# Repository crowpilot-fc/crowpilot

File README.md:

<!-- SPDX-License-Identifier: CC-BY-SA-4.0 -->
<!-- Copyright (C) 2026 Nitin Kumar -->

# CrowPilot

CrowPilot is an experimental fixed-wing flight controller for the RP2350A.
The rebuild is intentionally limited to one receiver protocol and one safe
bring-up path:

- WeAct RP2350A V10 controller module
- SBUS receiver input
- Eight standard PWM outputs
- MPU6500 over SPI
- BMP388 over I2C
- MicroSD blackbox logging
- Optional ESP32 field companion, electrically disabled while armed

The flight firmware is being rebuilt on the Raspberry Pi Pico SDK. It has not
been flight-tested. Do not install a propeller or connect a motor capable of
producing thrust during development or initial bench testing.

The current architecture and implementation plan are maintained in
[Notion](https://app.notion.com/p/3d0f4e695ae381d5b3c9dfaea4ba3e7e).
The authoritative physical BOM, wiring schedule, and staged assembly checks are
in the [Rebuild V1 bench carrier build pack](https://app.notion.com/p/3d0f4e695ae3812eb996db04cc5e7621).

## Host tests

```sh
cmake -S . -B build/host -G Ninja
cmake --build build/host
ctest --test-dir build/host --output-on-failure
```

## RP2350 firmware

Install the Raspberry Pi Pico SDK and Arm embedded toolchain, then run:

```sh
PICO_SDK_PATH=/path/to/pico-sdk cmake -S firmware -B build/firmware -G Ninja
cmake --build build/firmware
```

The first firmware milestone only implements safe PWM initialization, SBUS
manual passthrough, arming, receiver-loss failsafe, and a watchdog. Sensors,
logging, the companion, and stabilization are tracked as later milestones.

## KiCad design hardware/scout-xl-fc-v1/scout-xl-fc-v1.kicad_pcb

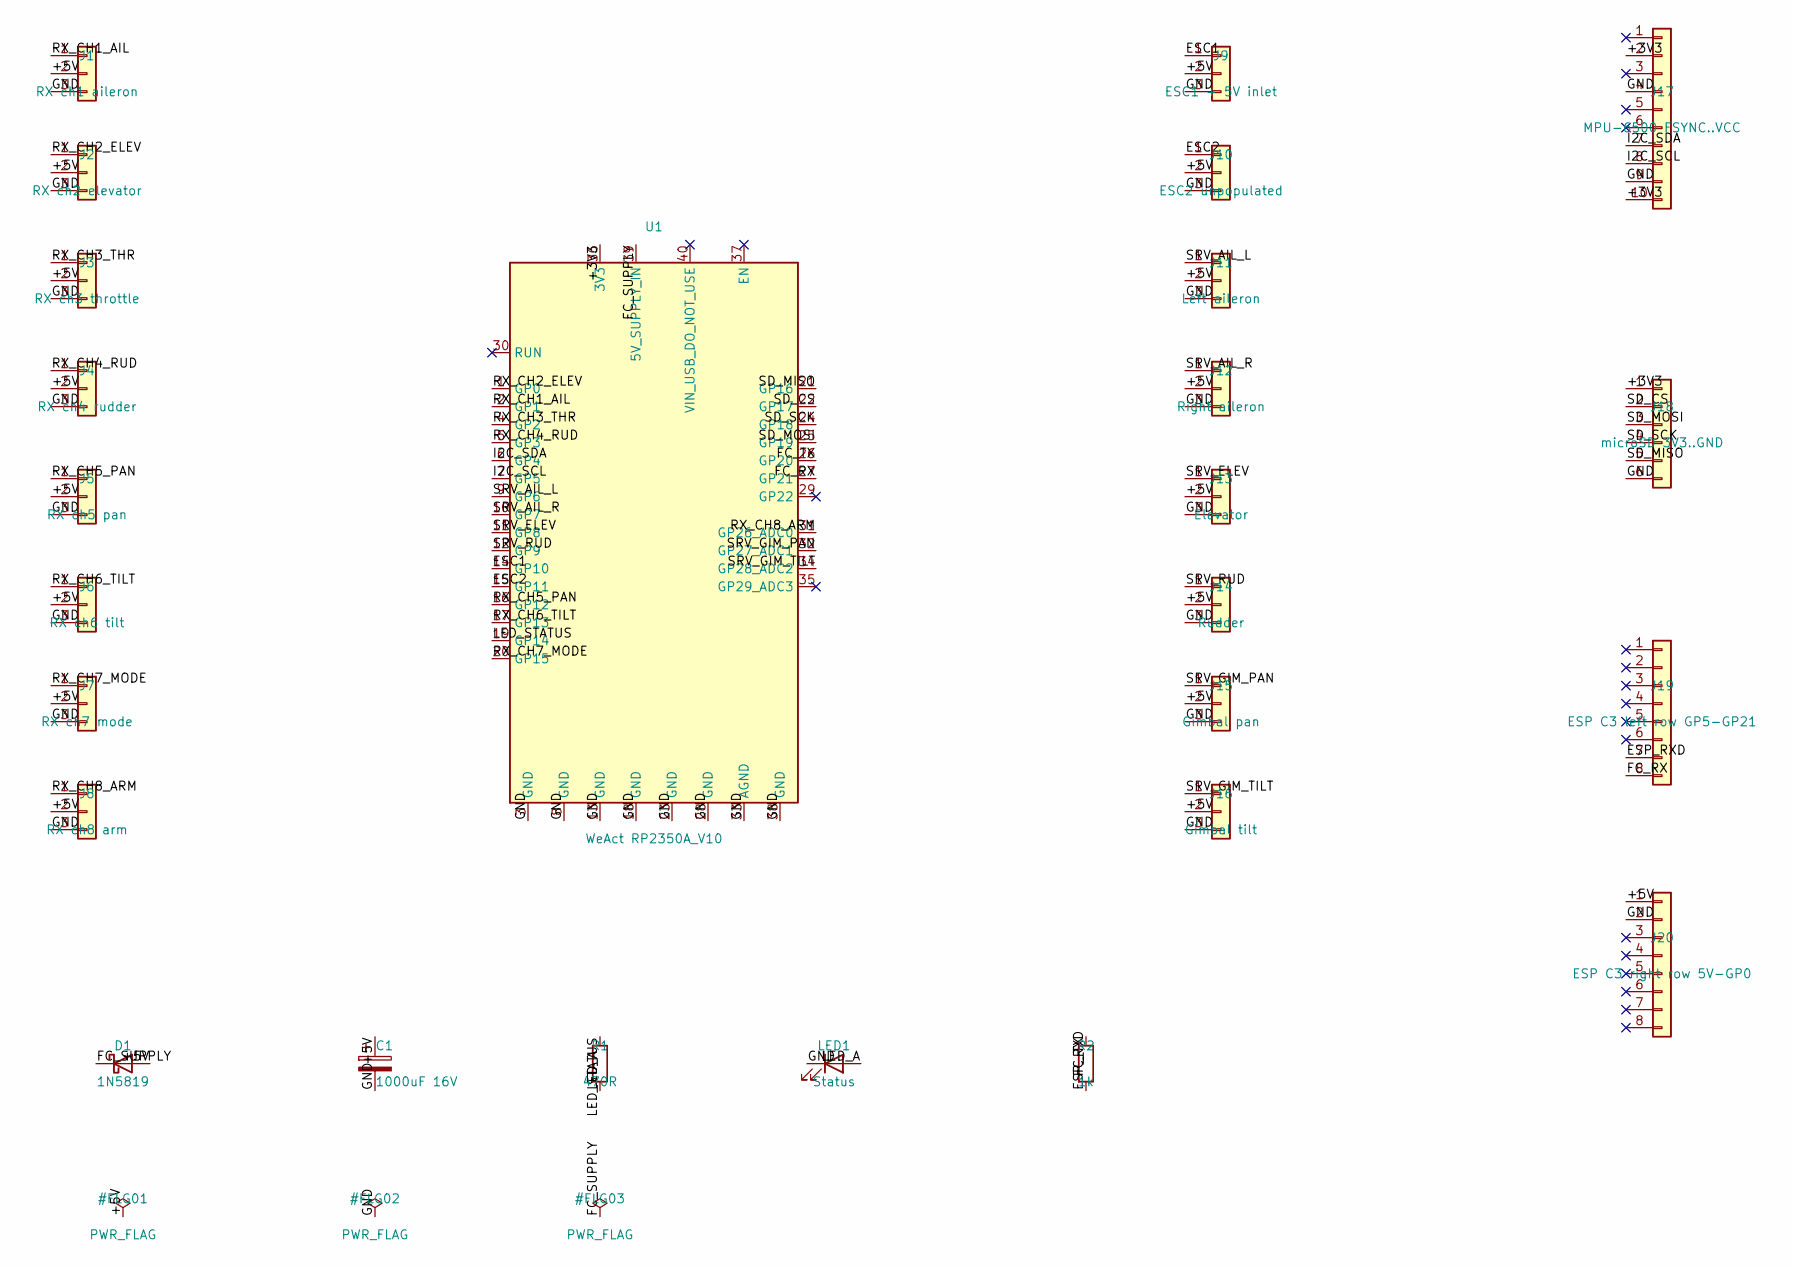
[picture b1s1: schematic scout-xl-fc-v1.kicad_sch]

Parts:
C1: 1000uF 16V; CP_Radial_D10.0mm_P5.00mm
D1: 1N5819; D_DO-41_SOD81_P10.16mm_Horizontal
J1: RX ch1 aileron; PinHeader_1x03_P2.54mm_Butt
J2: RX ch2 elevator; PinHeader_1x03_P2.54mm_Butt
J3: RX ch3 throttle; PinHeader_1x03_P2.54mm_Butt
J4: RX ch4 rudder; PinHeader_1x03_P2.54mm_Butt
J5: RX ch5 pan; PinHeader_1x03_P2.54mm_Butt
J6: RX ch6 tilt; PinHeader_1x03_P2.54mm_Butt
J7: RX ch7 mode; PinHeader_1x03_P2.54mm_Butt
J8: RX ch8 arm; PinHeader_1x03_P2.54mm_Butt
J9: ESC1 + 5V inlet; PinHeader_1x03_P2.54mm_Butt
J10: ESC2 unpopulated; PinHeader_1x03_P2.54mm_Butt
J11: Left aileron; PinHeader_1x03_P2.54mm_Butt
J12: Right aileron; PinHeader_1x03_P2.54mm_Butt
J13: Elevator; PinHeader_1x03_P2.54mm_Butt
J14: Rudder; PinHeader_1x03_P2.54mm_Butt
J15: Gimbal pan; PinHeader_1x03_P2.54mm_Butt
J16: Gimbal tilt; PinHeader_1x03_P2.54mm_Butt
J17: MPU-6500 FSYNC..VCC; PinHeader_1x10_P2.54mm_Vertical
J18: microSD 3V3..GND; PinHeader_1x06_P2.54mm_Vertical
J19: ESP C3 left row GP5-GP21; PinHeader_1x08_P2.54mm_Vertical
J20: ESP C3 right row 5V-GP0; PinHeader_1x08_P2.54mm_Vertical
LED1: Status; LED_D3.0mm_Clear
R1: 470R; R_Axial_DIN0207_L6.3mm_D2.5mm_P7.62mm_Horizontal
R2: 1k; R_Axial_DIN0207_L6.3mm_D2.5mm_P7.62mm_Horizontal
U1: WeAct RP2350A_V10; RaspberryPi_Pico_Common_THT

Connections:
+3V3: J17.2, J17.10, J18.1, U1.36 (3V3)
+5V: C1.1, D1.2 (A), J1.2, J2.2, J3.2, J4.2, J5.2, J6.2, J7.2, J8.2, J9.2, J10.2, J11.2, J12.2, J13.2, J14.2, J15.2, J16.2, J20.1
ESC1: J9.1, U1.14 (GP10)
ESC2: J10.1, U1.15 (GP11)
ESP_RXD: J19.7, R2.2
FC_RX: J19.8, U1.27 (GP21)
FC_SUPPLY: D1.1 (K), U1.39 (5V_SUPPLY_IN)
FC_TX: R2.1, U1.26 (GP20)
GND: C1.2, J1.3, J2.3, J3.3, J4.3, J5.3, J6.3, J7.3, J8.3, J9.3, J10.3, J11.3, J12.3, J13.3, J14.3, J15.3, J16.3, J17.4, J17.9, J18.6, J20.2, LED1.1 (K), U1.3 (GND), U1.8 (GND), U1.13 (GND), U1.18 (GND), U1.23 (GND), U1.28 (GND), U1.33 (AGND), U1.38 (GND)
I2C_SCL: J17.8, U1.7 (GP5)
I2C_SDA: J17.7, U1.6 (GP4)
LED_A: LED1.2 (A), R1.2
LED_STATUS: R1.1, U1.19 (GP14)
RX_CH1_AIL: J1.1, U1.2 (GP1)
RX_CH2_ELEV: J2.1, U1.1 (GP0)
RX_CH3_THR: J3.1, U1.4 (GP2)
RX_CH4_RUD: J4.1, U1.5 (GP3)
RX_CH5_PAN: J5.1, U1.16 (GP12)
RX_CH6_TILT: J6.1, U1.17 (GP13)
RX_CH7_MODE: J7.1, U1.20 (GP15)
RX_CH8_ARM: J8.1, U1.31 (GP26_ADC0)
SD_CS: J18.2, U1.22 (GP17)
SD_MISO: J18.5, U1.21 (GP16)
SD_MOSI: J18.3, U1.25 (GP19)
SD_SCK: J18.4, U1.24 (GP18)
SRV_AIL_L: J11.1, U1.9 (GP6)
SRV_AIL_R: J12.1, U1.10 (GP7)
SRV_ELEV: J13.1, U1.11 (GP8)
SRV_GIM_PAN: J15.1, U1.32 (GP27_ADC1)
SRV_GIM_TILT: J16.1, U1.34 (GP28_ADC2)
SRV_RUD: J14.1, U1.12 (GP9)

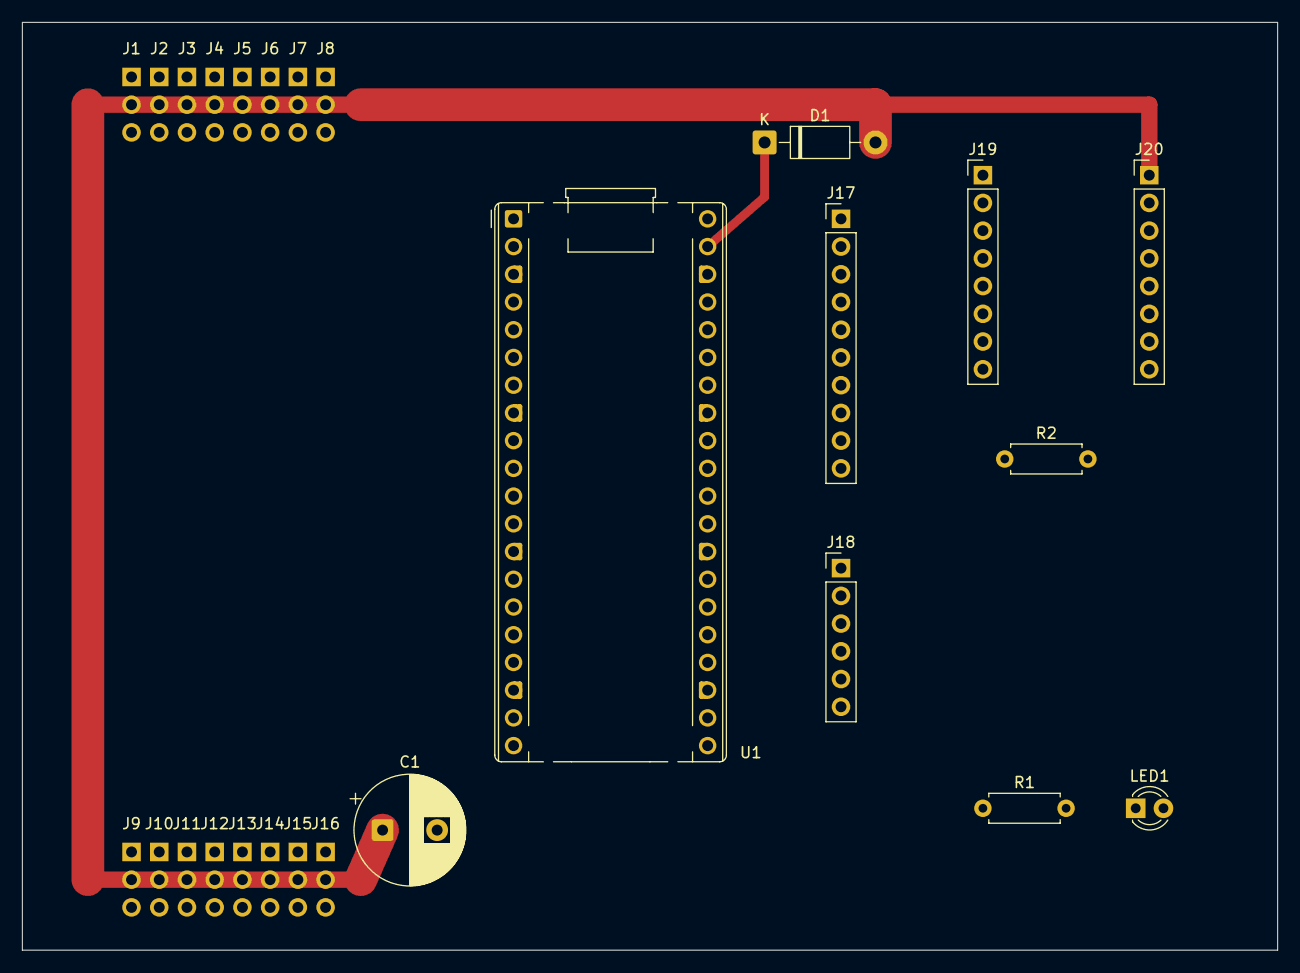
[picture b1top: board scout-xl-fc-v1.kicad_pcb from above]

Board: 2 copper layers, 115.0 x 85.0 mm, 26 parts (0 on the bottom side), 31 nets.

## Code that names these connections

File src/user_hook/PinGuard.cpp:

// SPDX-License-Identifier: GPL-3.0-or-later
// Copyright (C) 2026 Nitin Kumar

#include "src/user_hook/PinGuard.h"

#include <Arduino.h>

#include "src/Config.h"
#include "src/airframes/Airframe.h"

namespace cp::user_hook::pins {

namespace {

// One bit per GPIO. Set once a claimed-pin write has been warned about, so
// the warning fires at most once per pin per boot.
uint32_t s_warned_mask = 0;

void warnOnce(uint8_t pin) {
  if (pin < 32) {
    const uint32_t bit = 1UL << pin;
    if (s_warned_mask & bit) {
      return;
    }
    s_warned_mask |= bit;
  }
  if (Serial) {
    Serial.print("WARN: user_tick() write to firmware-claimed pin GP");
    Serial.print(pin);
    Serial.println(" ignored. See docs/reference/pin-maps.md for free pins.");
  }
}

}  // anonymous namespace

bool isClaimed(uint8_t pin) {
  if (pin == PIN_I2C_SDA   || pin == PIN_I2C_SCL)    return true;
  if (pin == PIN_MOTOR_RIGHT || pin == PIN_MOTOR_LEFT) return true;
  for (uint8_t i = 0; i < cp::airframes::N_SERVOS; ++i) {
    if (pin == PIN_SERVOS[i]) {
      return true;
    }
  }
  if (pin == PIN_SBUS_RX) return true;
  if (pin == PIN_SD_MOSI || pin == PIN_SD_MISO ||
      pin == PIN_SD_SCK  || pin == PIN_SD_CS)        return true;
  if (pin == PIN_LED_ONBOARD || pin == PIN_LED_STATUS) return true;
  if (pin == PIN_COMPANION_TX || pin == PIN_COMPANION_RX) return true;
#if ENABLE_LED_FLASHER
  if (pin == LED_FLASHER_PIN) return true;
#endif
#if ENABLE_BATTERY_MONITOR
  if (pin == BATTERY_ADC_PIN) return true;
#endif
#if BOARD_HAS_ESP_FLASH
  // The ESP passthrough flash path drives EN and IO0 only during the
  // `cp esp flash` command, but reserving them stops a user sketch from
  // wiring something else to those pins and getting random behaviour the
  // first time esp flash is run.
  if (pin == PIN_ESP_EN || pin == PIN_ESP_IO0) return true;
#endif
  return false;
}

void guardPinMode(uint8_t pin, uint8_t mode) {
  if (isClaimed(pin)) {
    warnOnce(pin);
    return;
  }
  pinMode(pin, mode);
}

void guardDigitalWrite(uint8_t pin, uint8_t value) {
  if (isClaimed(pin)) {
    warnOnce(pin);
    return;
  }
  digitalWrite(pin, value);
}

void guardAnalogWrite(uint8_t pin, int value) {
  if (isClaimed(pin)) {
    warnOnce(pin);
    return;
  }
  analogWrite(pin, value);
}

}  // namespace cp::user_hook::pins

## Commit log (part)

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2026-05-15 Add repo scaffolding: licenses, CI, and project files
    Add the license texts (GPL-3.0-or-later for code, CC-BY-SA-4.0 for
    documentation), the contributor and project documents, the GitHub issue
    and pull request templates, the SPDX-lint and docs CI workflows, the
    MkDocs configuration, and the .gitignore.
    The .gitignore excludes the clean-repo-handoff bundle so it is never
    committed to the repository.
2026-05-15 Add attitude estimation and IMU bias calibration
    Add the Madgwick six-degree-of-freedom AHRS, implemented from the
    Madgwick 2010 and 2011 papers. It fuses the gyro and accelerometer into
    a unit quaternion, seeds from the accelerometer for fast convergence,
    and renormalizes every step.
    The estimator exposes a quaternion attitude error that is continuous
    and singularity-free across the whole hover-to-forward transition, the
2026-05-15 Add the parameter registry, live tuning, and flash persistence
    Add the runtime parameter registry seeded from the Config.h defaults,
    the transmitter-channel live tuning of the PID gains, and the
    LittleFS-backed persistence of the registry.
    Reconcile the PID stabilizer with the live-tune contract: it now scales
    each blended proportional and derivative gain by the live-tune
    multipliers, so a transmitter knob adjusts the gains in flight. The
2026-05-16 Fix the transition channel direction
    The transition fader mapped the low channel pulse to hover, but the
    transmitter-setup and first-bench-test documentation both define the
    high pulse as hover. A pilot following the documentation would have had
    hover and forward reversed.
    Map the high pulse to hover, and move the failsafe transition default
    to 2000 us to match. Both must change together: with only the mapping
2026-05-16 Lower the provisional PID gains to a gentle starting point
    The provisional gains were Kp 0.5 for every axis. Roll and pitch
    stabilize on a degree-valued attitude error, so that saturates the
    controller at about two degrees of error; yaw stabilizes on a
    rate error in degrees per second, where 0.5 saturates even sooner.
    That contradicted the comment describing the values as sized for a
    gentle first powered test.
2026-05-16 Sync the config reference with the reviewed Config.h values
    The config-options reference and the flight-modes guide still carried
    the pre-review defaults. Earlier fixes changed the failsafe throttle and
    transition channel, the transition slew rate, the PID gain set, and the
    integral-limit meaning, but those edits never propagated to the docs.
    Update the failsafe, transition, and PID tables to the current Config.h
    values, and correct the flight-modes guide to the three-second
2026-05-16 Correct stale references and divergent values in carried docs
    Fixes a cluster of documentation that drifted from the built firmware:
    - wiring.md and Config.h: v1 supports inverted SBUS only. The PIO
    program is fixed to the inverted-SBUS polarity and RX_SBUS_INVERTED
    only XORs data bits, so a non-inverted receiver does not decode.
    - hardware-bom.md: note that the IMU driver gates init on WHO_AM_I and
    rejects clones, so a genuine MPU-6500 or MPU-6050 is required.
2026-05-16 Add v2 configurator: in-browser log viewer
    A Log tab that decodes a .BIN telemetry log in the browser, with no
    device connection needed.
    - log.js: a decoder for the 109-byte telemetry record, mirroring the
    schema in tools/log_analyzer/decode_features.py. Computes a summary
    (duration, loop-period health, armed fraction, failsafe events, gyro
    RMS, flight-mode breakdown) and can generate a synthetic sample log.
2026-05-18 Configure firmware and SITL for the DHC-4 Caribou first-flight build
    Select the WeAct RP2350A_V10 board and the twin-engine cargo plane
    airframe, and enable the fixed-wing stabilizer, since the first
    hardware to fly CrowPilot is a DHC-4 Caribou.
    Add MOTOR_PROTOCOL so the motor pins can be driven as standard
    1000 to 2000 us PWM as well as OneShot125. The Caribou ESCs do not
    support OneShot, so the build defaults to PWM. The ESC pulse
2026-05-18 Accept SBUS2 end bytes in the frame parser
    The frame validator rejected any frame whose 25th byte was not 0x00.
    Standard SBUS1 receivers send 0x00, but SBUS2 receivers send a
    non-zero end byte to carry telemetry-slot information, so every frame
    from such a receiver was counted as lost and would trip the
    link-loss failsafe. Accept 0x00 and the SBUS2 end bytes (low nibble
    0x4).
2026-05-18 Run the cp configurator protocol on the companion UART
    The cp serial CLI ran only on USB. Add a second channel on the
    companion UART (Serial2, the board's companion pins), gated by
    ENABLE_COMPANION_CLI on native builds, so an ESP WiFi module can
    bridge the same protocol to a phone.
    The CLI now tracks two channels with independent line buffers;
    replies go back to the channel that issued the command. Telemetry
2026-05-21 Add Caribou bench-test procedure
    A plane-specific pre-flight procedure for the DHC-4 Caribou. Phases
    cover pre-power inspection, TX channel mapping, USB smoke test,
    receiver verification, battery power-on, the wireless companion, the
    critical surface-direction check, throttle range, the arm-edge
    sequence, the failsafe drill, the user-sketch aux channels, the
    stabilizer behaviour test, the telemetry log, and a final go/no-go
2026-05-21 Add fixed-wing tuning section to the public tuning guide
    The public tuning page covered only the tailsitter angle PID. Bring
    the plane tuning procedure forward from internal-docs/TUNING.md so a
    plane pilot has the right reference at the bench.
    Adds two sections at the end of docs/user-guide/tuning.md:
    - Plane tuning (fixed-wing airframes). Covers the plane stabilizer
    gains (KP_STAB_*, KD_STAB_*, KP_ALT, KD_ALT) and a six-step tuning
2026-05-23 Reframe docs around the Caribou plane as the current airframe
    The docs still presented the tailsitter as the v1.0 default and the
    fixed-wing plane as unshipped v1.1 work, but the firmware ships
    configured for the DHC-4 Caribou and the plane subsystem, mixer, user
    hook, ESP companion, and phone UI have all landed.
    Rewrite the fixed-wing-plane page to describe the live airframe, demote
    the tailsitter to the carried alternate, update the what-is-crowpilot and
2026-05-25 Give the Pico 2 W onboard WiFi full cp parity with the ESP companion
    The onboard WiFi now does everything the RP2350 + ESP32-C3 pair does: it
    serves the same phone UI and bridges the same cp protocol, just core1 to
    core0 instead of ESP to UART.
    Core1 raises the AP, serves the shared web UI (the ESP companion's
    web_ui.h, included verbatim so the two never drift, its WebSocket targets
    location.hostname:81 so it works from either host), and runs a
2026-05-25 Complete the filtering stack: shared module, gyro notch, D-term low-pass
    Add src/libs/Filter.h with two reusable primitives: a PT1 first-order
    low-pass and an RBJ biquad notch. Refactor the estimator's gyro low-pass
    to use the shared PT1, and add a per-axis gyro notch ahead of it for
    removing a measured motor or propeller vibration peak (GYRO_NOTCH_CENTER_HZ,
    default 0 / disabled until a peak is measured). Add a per-axis D-term
    low-pass in the PID (DTERM_LPF_CUTOFF_HZ, default 60 Hz), since the
2026-05-26 Add a WeAct/Caribou pin map to the wiring guide
    The wiring guide led with the Waveshare RP2350-Tiny, whose servos are on
    GP12 and GP13, but the default first-flight build is the DHC-4 Caribou on a
    WeAct RP2350A_V10, where the servos are on GP6 to GP9. A builder on the
    WeAct following the Tiny table would wire the surfaces to the wrong pins.
    Add a WeAct/Caribou pin map as the primary table, with the firmware pins
    and a separate table for the Caribou aux pins driven by user-sketch.ino,
2026-05-27 Document CRSF receiver support
    CRSF (Crossfire / ELRS) is now implemented, so the docs no longer call it a
    reserved stub. Update the landing page, config-options, transmitter setup,
    wiring guide, hardware BOM, roadmap, and changelog to present SBUS and CRSF
    as the two supported receiver protocols chosen by RX_PROTOCOL, with CRSF as
    the recommended path for ELRS gear. Generalize the wiring guide's SBUS
    receiver section to cover both. PPM and PWM remain reserved.
2026-05-27 Document bidirectional DShot and the dynamic notch
    Cover both new features across the public docs. The config-options reference
    gains the gyro-filter rows (the static low-pass and notch, previously
    undocumented) plus the dynamic-notch and bidirectional-DShot options. The
    index motor section, the wiring ESC section, and the algorithms gyro-filtering
    and motor-output sections explain how the RPM-tracking notch and the
    bidirectional eRPM path work. Both changelogs note the additions. Throughout,
2026-05-27 Harden the Pico 2 W cross-core byte ring
    The SPSC ring's consumer read head_ and then read the data with no barrier
    between, so on the ARMv8-M memory model the data load could be observed before
    the index load and return a stale byte. Add an acquire barrier in pop() after
    the head_ check, pairing it with the producer's existing release before head_
    advances.
    The WebSocket ingress also ignored push() failures, so a frame larger than the
2026-05-28 Add a simple fixed-wing plane setup guide
    The first of a per-build-type setup family under getting-started: wiring tables
    for the Tiny and NEO, the one-or-two aileron options (two outputs is the
    default, a Y harness with one reversed servo is the minimalist route), the
    5/6/8-channel plan with the Config.h remaps, the flight modes, and how to tune
    the plane gains (Config.h today, since the live-tune knobs and configurator
    sliders reach only the tailsitter PID for now). Linked from the docs landing
2026-05-29 Add per-servo output config (reverse, subtrim, endpoints)
    Optional per-surface trim in the actuator output stage, indexed by the
    airframe's SERVO_* slot: reverse for a backward-mounted servo, a microsecond
    subtrim, and per-servo travel endpoints, with a final clamp to an absolute safe
    pulse range. Gated by ENABLE_SERVO_CONFIG, off by default, when the single
    SERVO_MIN_US/SERVO_MAX_US range applies to every servo as before. servoPulseUs
    is now per-servo and static-asserts the config arrays fit the airframe. Pilot
2026-05-31 Path B: harden first boot so a bare FC always does something visible
    Five fixes so a CrowPilot FC powered up with nothing else wired produces
    a clear diagnostic instead of silently locking up:
    build.sh: pass a flash partition by default (4 MB total, 1 MB sketch,
    3 MB FS). The previous default reserved 0 bytes for the FS, so the
    runtime parameter store's LittleFS.begin() had nowhere to mount and
    hung the firmware at boot. Override with CROWPILOT_FLASH for other
2026-06-03 Audit fixes: baro_scan moves to CLI, I2C recovery reports its status
    audit said the baro chip-id scan was using HAL as a formatting layer.
    moved the I2C probing and hex dump into doScan() in src/cli/Cli.cpp,
    where bench formatting belongs. baro_scan removed from cp::hal. HAL
    stays a pure abstraction over the bus; CLI does the talking. SITL
    stub also drops.
    audit also said the I2C bus-recovery routine pulses SCL and then
2026-06-03 Audit Tier 1: per-airframe failsafe + async SD logging on core 1
    Two pieces of work that finish the Tier 1 audit list.
    Per-airframe failsafe (src/Config.h FS_* block). The previous failsafe
    held throttle at 1300 us with the arm channel armed-side for every
    airframe. That is correct for the tailsitter (powered descent on hover)
    but wrong for fixed-wing (a powered, sticks-centred plane wanders out
    of range until it hits something) and not great for a quad either. The
